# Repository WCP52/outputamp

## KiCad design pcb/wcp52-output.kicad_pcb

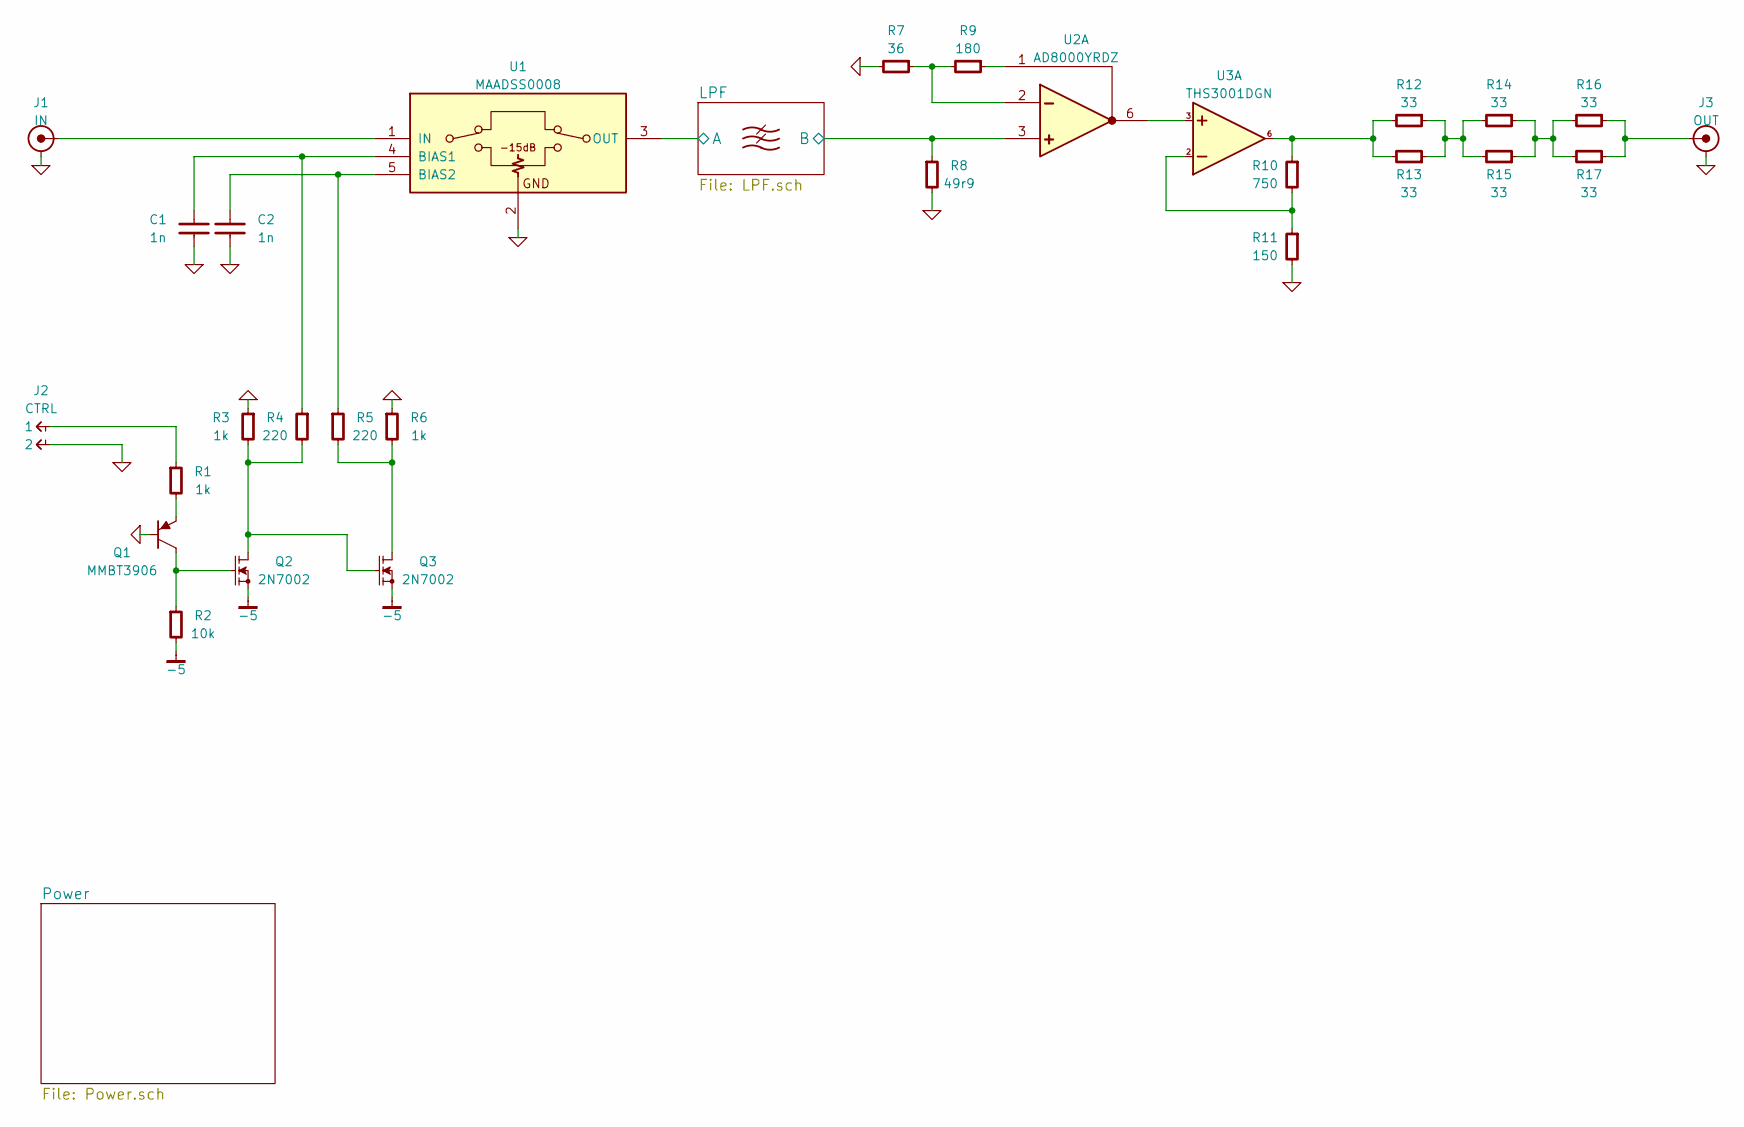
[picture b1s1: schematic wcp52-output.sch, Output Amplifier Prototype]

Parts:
C1, C2: 1n; CAPC1005X55
J1: IN; CONN-2_CONSMA001
J2: CTRL; CONN_2-SIL
J3: OUT; CONN-2_CONSMA001
Q1: MMBT3906; SOT-23
Q2, Q3: 2N7002; SOT-23
R1, R3, R6: 1k; RESC1005X40
R2: 10k; RESC1005X40
R4, R5: 220; RESC1005X40
R7: 36; RESC1005X40
R8: 49r9; RESC1005X40
R9: 180; RESC1005X40
R10: 750; RESC1005X40
R11: 150; RESC1005X40
R12, R13, R14, R15, R16, R17: 33; RESC1608X50
U1: MAADSS0008; SOT-23-5
U2: AD8000YRDZ; SOIC127P600X175-9
U3: THS3001DGN; SOP65P490X110-9A

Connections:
-5: Q2.2, Q3.2, R2.2; also elsewhere on the board
/LPF/A: U1.3 (OUT); also elsewhere on the board
/LPF/B: R8.1, U2.3; also elsewhere on the board
GND: C1.2, C2.2, J1.2, J2.2, J3.2, Q1.1, R3.1, R6.1, R7.2, R8.2, R11.2, U1.2, U2.9; also elsewhere on the board
unnamed: C1.1, R4.1, U1.4 (BIAS1)
unnamed: C2.1, R5.1, U1.5 (BIAS2)
unnamed: J1.1, U1.1 (IN)
unnamed: J2.1, R1.1
unnamed: J3.1, R16.1, R17.1
unnamed: Q1.2, R1.2
unnamed: Q1.3, Q2.1, R2.1
unnamed: Q2.3, Q3.1, R3.2, R4.2
unnamed: Q3.3, R5.2, R6.2
unnamed: R7.1, R9.2, U2.2
unnamed: R9.1, U2.1
unnamed: R10.1, R12.2, R13.2, U3.6
unnamed: R10.2, R11.1, U3.2
unnamed: R12.1, R13.1, R14.2, R15.2
unnamed: R14.1, R15.1, R16.2, R17.2
unnamed: U2.6, U3.3

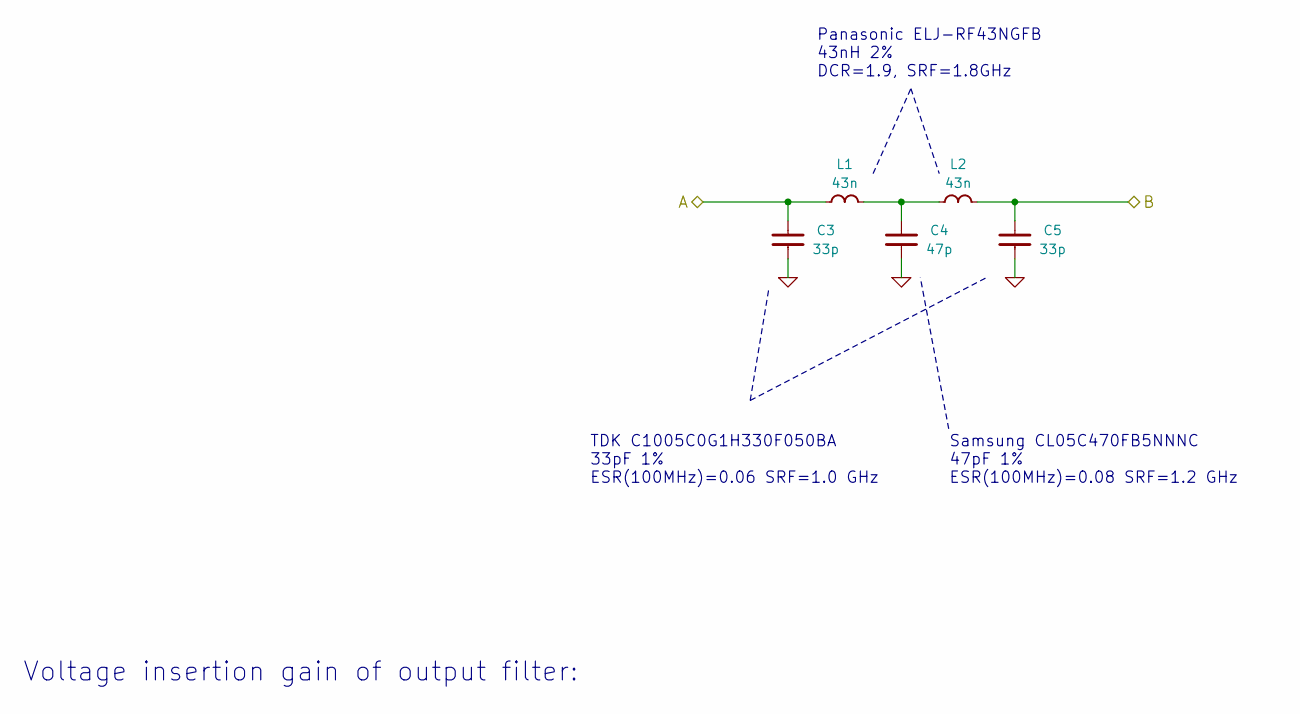
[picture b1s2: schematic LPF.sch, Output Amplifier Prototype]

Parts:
C3, C5: 33p; CAPC1005X55
C4: 47p; CAPC1005X55
L1, L2: 43n; INDC1005X60

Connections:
/LPF/A: C3.1, L1.2; also elsewhere on the board
/LPF/B: C5.1, L2.1; also elsewhere on the board
GND: C3.2, C4.2, C5.2; also elsewhere on the board
unnamed: C4.1, L1.1, L2.2

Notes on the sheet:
Panasonic ELJ-RF43NGFB 43nH 2% DCR=1.9, SRF=1.8GHz
TDK C1005C0G1H330F050BA 33pF 1% ESR(100MHz)=0.06 SRF=1.0 GHz
Samsung CL05C470FB5NNNC 47pF 1% ESR(100MHz)=0.08 SRF=1.2 GHz
Voltage insertion gain of output filter:

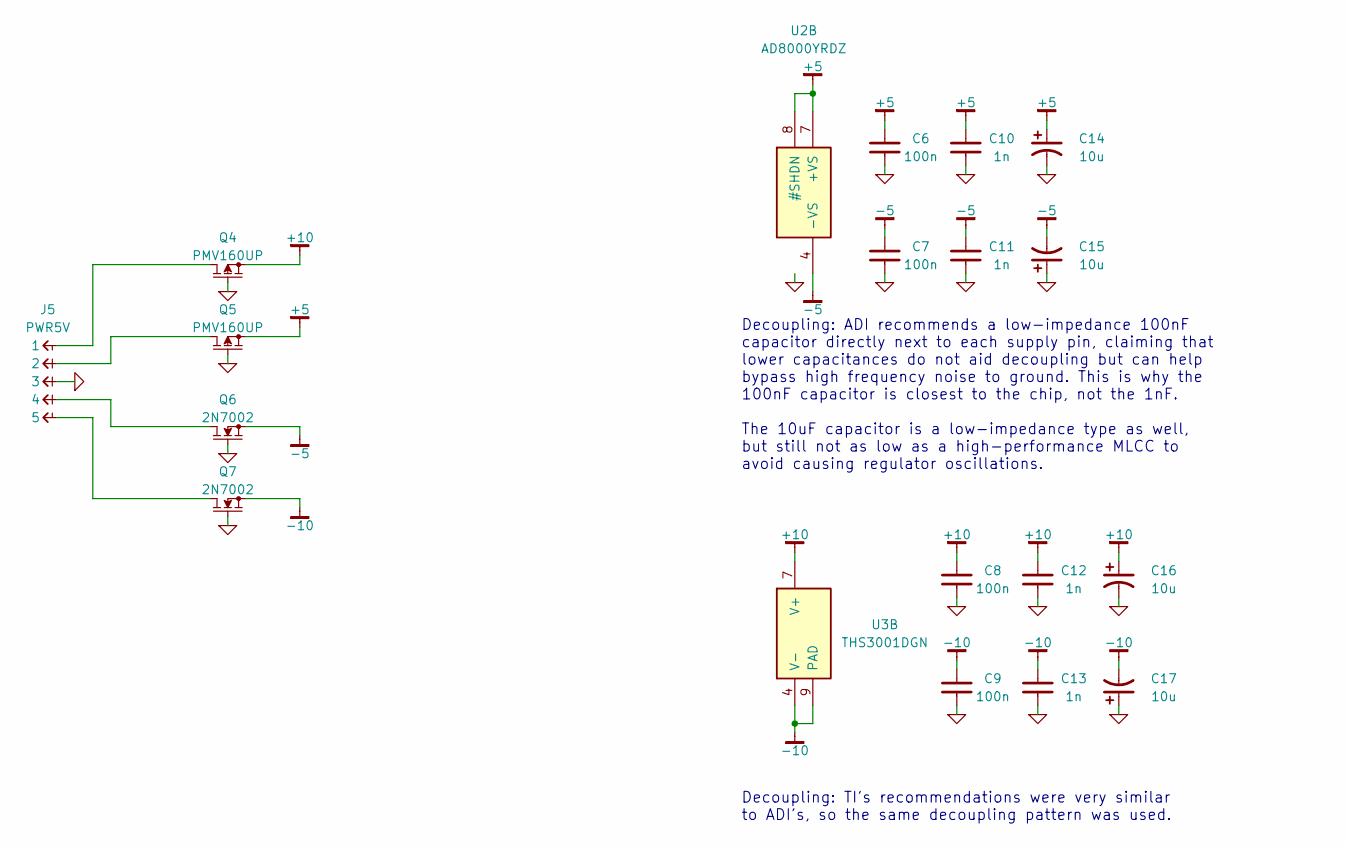
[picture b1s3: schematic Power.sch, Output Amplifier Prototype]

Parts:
C6, C7, C8, C9: 100n; CAPC2012X70
C10, C11, C12, C13: 1n; CAPC1005X55
C14, C15, C16, C17: 10u; C-ALUM-5mm
J5: PWR5V; CONN_5-SIL
Q4, Q5: PMV160UP; SOT-23
Q6, Q7: 2N7002; SOT-23
U2: AD8000YRDZ; SOIC127P600X175-9
U3: THS3001DGN; SOP65P490X110-9A

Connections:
+5: C6.1, C10.1, C14.1, Q5.2, U2.7 (+VS), U2.8 (#SHDN)
+10: C8.1, C12.1, C16.1, Q4.2, U3.7 (V+)
-5: C7.1, C11.1, C15.2, Q6.2, U2.4 (-VS); also elsewhere on the board
-10: C9.1, C13.1, C17.2, Q7.2, U3.4 (V-), U3.9 (PAD)
GND: C6.2, C7.2, C8.2, C9.2, C10.2, C11.2, C12.2, C13.2, C14.2, C15.1, C16.2, C17.1, J5.3, Q4.1, Q5.1, Q6.1, Q7.1, U2.9; also elsewhere on the board
unnamed: J5.1, Q4.3
unnamed: J5.2, Q5.3
unnamed: J5.4, Q6.3
unnamed: J5.5, Q7.3

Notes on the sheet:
Decoupling: ADI recommends a low-impedance 100nF capacitor directly next to each supply pin, claiming that lower capacitances do not aid decoupling but can help bypass high frequency noise to ground. This is why the 100nF capacitor is closest to the chip, not the 1nF. The 10uF capacitor is a low-im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
Decoupling: TI's recommendations were very similar to ADI's, so the same decoupling pattern was used.

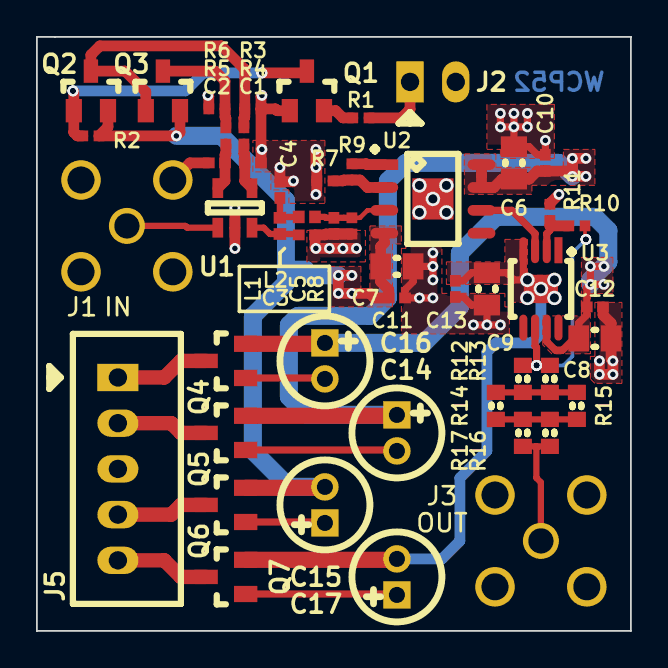
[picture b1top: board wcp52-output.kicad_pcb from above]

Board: 4 copper layers, 33.0 x 33.0 mm, 50 parts (0 on the bottom side), 28 nets.

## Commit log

2014-11-08 Added simulation
2014-11-16 Some schematic work
2014-11-16 Copper is likely complete
2014-11-16 Silkscreen touchups
2014-11-16 Touchups
2014-11-16 Removed old comment from schematic
2014-11-17 More PCB touchups
2014-11-17 Fixed FET part numbers
2015-02-17 Added simulation of elliptical filter
